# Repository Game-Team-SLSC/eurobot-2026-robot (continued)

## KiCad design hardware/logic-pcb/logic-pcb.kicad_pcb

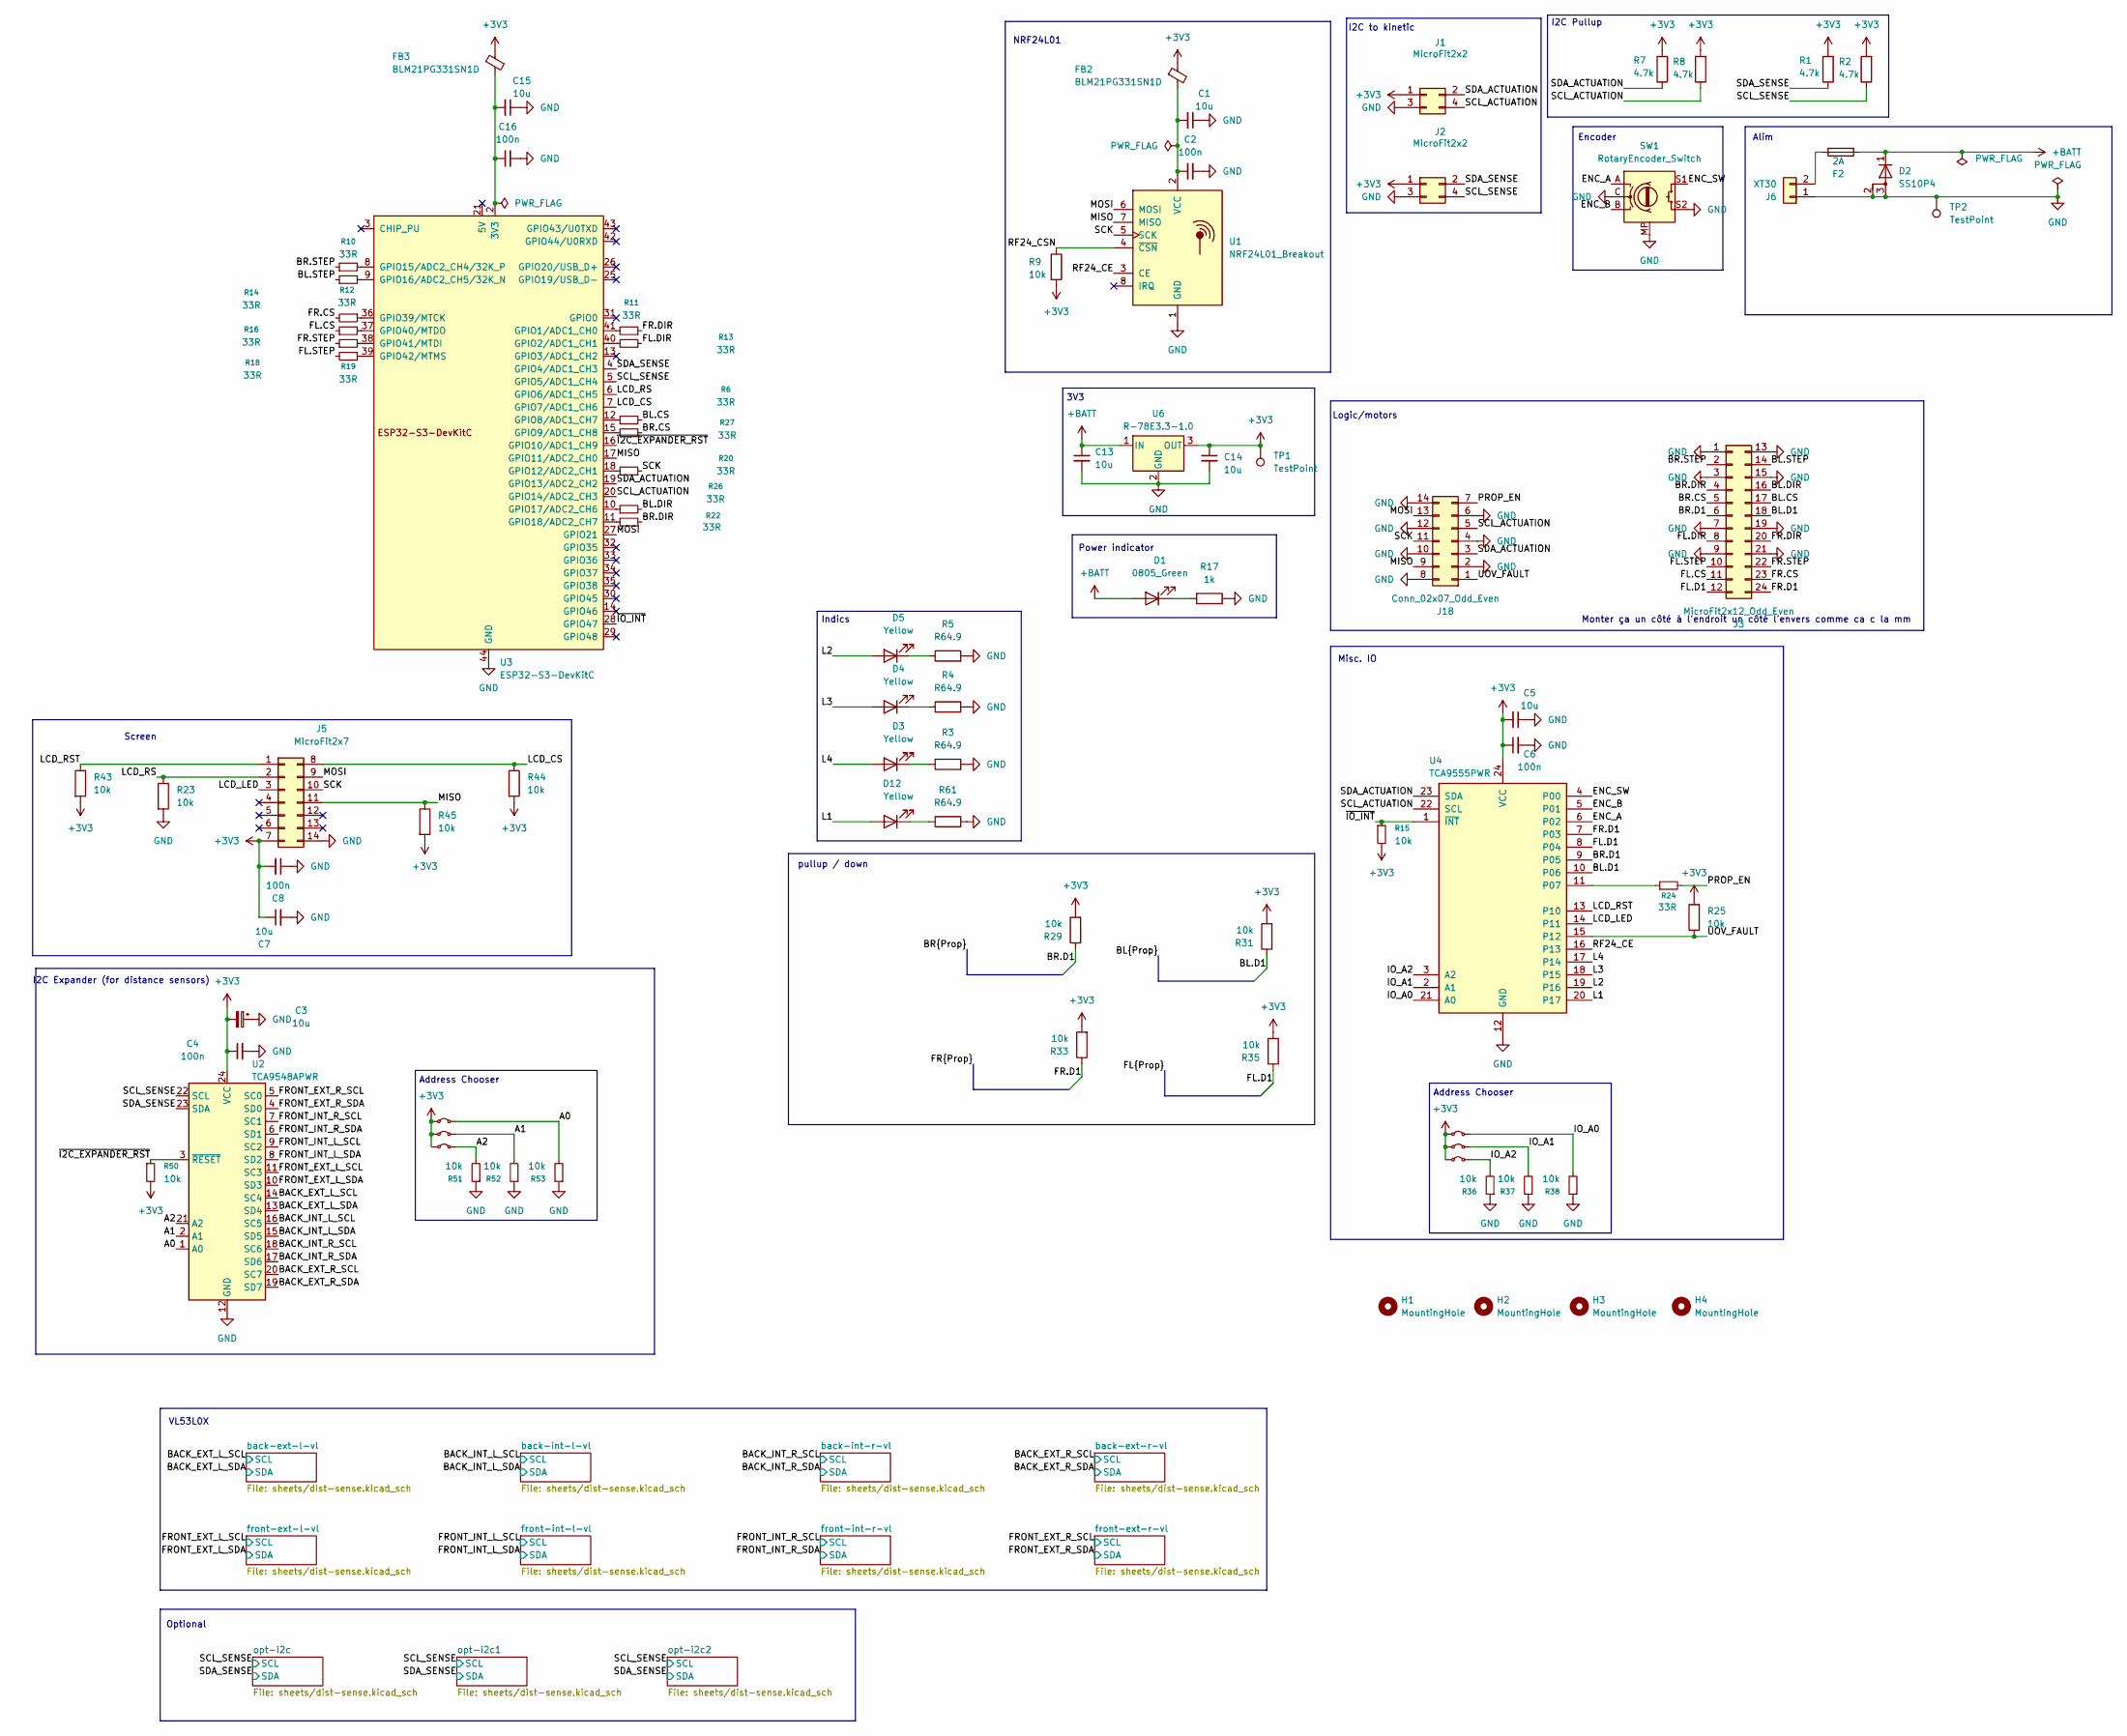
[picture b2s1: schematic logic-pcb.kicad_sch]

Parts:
C1, C3, C5, C7, C13, C14, C15: 10u; C_0805_2012Metric_Pad1.18x1.45mm_HandSolder; MPN CL21A106KBYQNNE
C2, C4, C6, C8, C16: 100n; C_0805_2012Metric_Pad1.18x1.45mm_HandSolder; MPN CL21B104KBCNNND
D1: 0805_Green; LED_0805_2012Metric_Pad1.15x1.40mm_HandSolder; MPN APA2106ZGCK
D2: SS10P4; SS10P4M387A; MPN SS10P4-M3/87A
D3, D4, D5, D12: Yellow; LED_0805_2012Metric_Pad1.15x1.40mm_HandSolder; MPN APA2106SYCK
F2: 2A; Fuseholder_Cylinder-5x20mm_Schurter_0031_8201_Horizontal_Op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
FB2, FB3: BLM21PG331SN1D; L_0805_2012Metric_Pad1.05x1.20mm_HandSolder; MPN BLM21PG331SN1D
H1, H2, H3, H4: MountingHole; MountingHole_3.2mm_M3
J1, J2: MicroFit2x2; J_Wurth_WR-MPC3_66200421122; MPN 66200421122
J3: MicroFit2x12_Odd_Even; J_Wurth_WR-MPC3_66202421122; MPN 43045-2412
J5: MicroFit2x7; J_Wurth_WR-MPC3_66201421122; MPN 43045-1412
J6: XT30; AMASS_XT30U-M_1x02_P5.0mm_Vertical
J18: Conn_02x07_Odd_Even; J_Wurth_WR-MPC3_66201421122; MPN 43045-1412
NT1, NT2, NT3, NT10, NT11, NT12: Jumper_2_Bridged; TestPoint_2Pads_Pitch2.54mm_Drill0.8mm; MPN M7582-46
R1, R2, R7, R8: 4.7k; R_0805_2012Metric_Pad1.20x1.40mm_HandSolder; MPN CRCW08054K70FKEA
R3, R4, R5, R61: R64.9; R_0805_2012Metric_Pad1.20x1.40mm_HandSolder; MPN CRCW08051K00FKEA
R6, R10, R11, R12, R13, R14, R16, R18, R19, R20, R22, R24, R26, R27: 33R; R_0805_2012Metric_Pad1.20x1.40mm_HandSolder; MPN CRCW080533R0FKEA
R9, R15, R23, R25, R29, R31, R33, R35, R36, R37, R38, R43, R44, R45, R50, R51, R52, R53: 10k; R_0805_2012Metric_Pad1.20x1.40mm_HandSolder; MPN CRCW080510K0FKEA
R17: 1k; R_0805_2012Metric_Pad1.20x1.40mm_HandSolder; MPN CRCW08051K00FKEA
SW1: RotaryEncoder_Switch; RotaryEncoder_Alps_EC11E-Switch_Vertical_H20mm; MPN EC11E15204A3
TP1, TP2: TestPoint; TestPoint_THTPad_D1.0mm_Drill0.5mm
U1: NRF24L01_Breakout; nRF24L01+_Breakout
U2: TCA9548APWR; TSSOP-24_4.4x7.8mm_P0.65mm; MPN TCA9548APWR
U3: ESP32-S3-DevKitC; MPN ESP32-S3-DevKitC-1-N8R8
U4: TCA9555PWR; TSSOP-24_4.4x7.8mm_P0.65mm; MPN TCA9555PWR
U6: R-78E3.3-1.0; Converter_DCDC_RECOM_R-78E-0.5_THT; MPN R-78E3.3-1.0

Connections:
+3V3: C3.2, C4.1, C5.2, C6.1, C7.1, C8.2, C14.1, FB2.1, FB3.1, J1.1, J2.1, J5.7, NT1.1 (A), NT2.1 (A), NT3.1 (A), NT10.1 (A), NT11.1 (A), NT12.1 (A), R1.2, R2.2, R7.2, R8.2, R9.2, R15.2, R25.2, R29.2, R31.2, R33.2, R35.2, R43.2, R44.2, R45.2, R50.2, TP1.1, U2.24 (VCC), U4.24 (VCC), U6.3 (OUT); also elsewhere on the board
+BATT: C13.1, D1.2 (A), D2.1 (K), F2.2, U6.1 (IN)
/A0: NT10.2 (B), R53.2, U2.1 (A0)
/A1: NT11.2 (B), R52.2, U2.2 (A1)
/A2: NT12.2 (B), R51.2, U2.21 (A2)
/BACK_EXT_L_SCL: U2.14 (SC4); also elsewhere on the board
/BACK_EXT_L_SDA: U2.13 (SD4); also elsewhere on the board
/BACK_EXT_R_SCL: U2.20 (SC7); also elsewhere on the board
/BACK_EXT_R_SDA: U2.19 (SD7); also elsewhere on the board
/BACK_INT_L_SCL: U2.16 (SC5); also elsewhere on the board
/BACK_INT_L_SDA: U2.15 (SD5); also elsewhere on the board
/BACK_INT_R_SCL: U2.18 (SC6); also elsewhere on the board
/BACK_INT_R_SDA: U2.17 (SD6); also elsewhere on the board
/BL.CS: J3.17, R6.2
/BL.D1: J3.18, R31.1, U4.10 (P06)
/BL.DIR: J3.16, R26.2
/BL.STEP: J3.14, R12.1
/BR.CS: J3.5, R27.2
/BR.D1: J3.6, R29.1, U4.9 (P05)
/BR.DIR: J3.4, R22.2
/BR.STEP: J3.2, R10.1
/ENC_A: SW1.A, U4.6 (P02)
/ENC_B: SW1.B, U4.5 (P01)
/ENC_SW: SW1.S1, U4.4 (P00)
/FL.CS: J3.11, R16.1
/FL.D1: J3.12, R35.1, U4.8 (P04)
/FL.DIR: J3.8, R13.1
/FL.STEP: J3.10, R19.2
/FR.CS: J3.23, R14.2
/FR.D1: J3.24, R33.1, U4.7 (P03)
/FR.DIR: J3.20, R11.1
/FR.STEP: J3.22, R18.1
/FRONT_EXT_L_SCL: U2.11 (SC3); also elsewhere on the board
/FRONT_EXT_L_SDA: U2.10 (SD3); also elsewhere on the board
/FRONT_EXT_R_SCL: U2.5 (SC0); also elsewhere on the board
/FRONT_EXT_R_SDA: U2.4 (SD0); also elsewhere on the board
/FRONT_INT_L_SCL: U2.9 (SC2); also elsewhere on the board
/FRONT_INT_L_SDA: U2.8 (SD2); also elsewhere on the board
/FRONT_INT_R_SCL: U2.7 (SC1); also elsewhere on the board
/FRONT_INT_R_SDA: U2.6 (SD1); also elsewhere on the board
/IO_A0: NT1.2 (B), R38.2, U4.21 (A0)
/IO_A1: NT2.2 (B), R37.2, U4.2 (A1)
/IO_A2: NT3.2 (B), R36.2, U4.3 (A2)
/L1: D12.2 (A), U4.20 (P17)
/L2: D5.2 (A), U4.19 (P16)
/L3: D4.2 (A), U4.18 (P15)
/L4: D3.2 (A), U4.17 (P14)
/LCD_CS: J5.8, R44.1, U3.7 (GPIO7/ADC1_CH6)
/LCD_LED: J5.3, U4.14 (P11)
/LCD_RS: J5.2, R23.1, U3.6 (GPIO6/ADC1_CH5)
/LCD_RST: J5.1, R43.1, U4.13 (P10)
/MISO: J5.11, J18.9, R45.1, U1.7 (MISO), U3.17 (GPIO11/ADC2_CH0)
/MOSI: J5.9, J18.13, U1.6 (MOSI), U3.27 (GPIO21)
/PROP_EN: J18.7, R24.2
/RF24_CE: U1.3 (CE), U4.16 (P13)
/RF24_CSN: R9.1, U1.4 (~CSN)
/SCK: J5.10, J18.11, R20.1, U1.5 (SCK)
/SCL_ACTUATION: J1.4, J18.5, R8.1, U3.20 (GPIO14/ADC2_CH3), U4.22 (SCL)
/SCL_SENSE: J2.4, R2.1, U2.22 (SCL), U3.5 (GPIO5/ADC1_CH4); also elsewhere on the board
/SDA_ACTUATION: J1.2, J18.3, R7.1, U3.19 (GPIO13/ADC2_CH2), U4.23 (SDA)
/SDA_SENSE: J2.2, R1.1, U2.23 (SDA), U3.4 (GPIO4/ADC1_CH3); also elsewhere on the board
/UOV_FAULT: J18.1, R25.1, U4.15 (P12)
/~I2C_EXPANDER_RST: R50.1, U2.3 (~RESET), U3.16 (GPIO10/ADC1_CH9)
/~IO_INT: R15.1, U3.28 (GPIO47), U4.1 (~INT)
GND: C1.1, C2.2, C3.1, C4.2, C5.1, C6.2, C7.2, C8.1, C13.2, C14.2, C15.1, C16.2, D2.2 (A), D2.3 (A), J1.3, J2.3, J3.1, J3.3, J3.7, J3.9, J3.13, J3.15, J3.19, J3.21, J5.14, J6.1, J18.2, J18.4, J18.6, J18.8, J18.10, J18.12, J18.14, R3.2, R4.2, R5.2, R17.2, R23.2, R36.1, R37.1, R38.1, R51.1, R52.1, R53.1, R61.2, SW1.C, SW1.MP, SW1.S2, TP2.1, U1.1 (GND), U2.12 (GND), U3.22 (GND), U3.23 (GND), U3.24 (GND), U3.44 (GND), U4.12 (GND), U6.2 (GND); also elsewhere on the board
unnamed: C15.2, C16.1, FB3.2, U3.1 (3V3), U3.2 (3V3)
unnamed: D1.1 (K), R17.1
unnamed: D3.1 (K), R3.1
unnamed: D4.1 (K), R4.1
unnamed: D5.1 (K), R5.1
unnamed: D12.1 (K), R61.1
unnamed: F2.1, J6.2
unnamed: C1.2, C2.1, FB2.2, U1.2 (VCC)
unnamed: R11.2, U3.41 (GPIO1/ADC1_CH0)
unnamed: R13.2, U3.40 (GPIO2/ADC1_CH1)
unnamed: R6.1, U3.12 (GPIO8/ADC1_CH7)
unnamed: R27.1, U3.15 (GPIO9/ADC1_CH8)
unnamed: R20.2, U3.18 (GPIO12/ADC2_CH1)
unnamed: R10.2, U3.8 (GPIO15/ADC2_CH4/32K_P)
unnamed: R12.2, U3.9 (GPIO16/ADC2_CH5/32K_N)
unnamed: R26.1, U3.10 (GPIO17/ADC2_CH6)
unnamed: R22.1, U3.11 (GPIO18/ADC2_CH7)
unnamed: R14.1, U3.36 (GPIO39/MTCK)
unnamed: R16.2, U3.37 (GPIO40/MTDO)
unnamed: R18.2, U3.38 (GPIO41/MTDI)
unnamed: R19.1, U3.39 (GPIO42/MTMS)
unnamed: R24.1, U4.11 (P07)

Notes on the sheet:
Address Chooser
VL53L0X
I2C Expander (for distance sensors)
Monter ça un côté à l'endroit un côté l'envers comme ca c la mm
Logic/motors
Indics
Alim
3V3
I2C Pullup
Misc. IO
pullup / down
Optional
Screen
NRF24L01
Encoder
Power indicator
I2C to kinetic

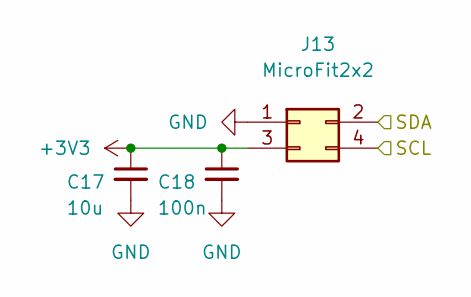
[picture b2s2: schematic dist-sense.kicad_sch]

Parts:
C17: 10u; C_0805_2012Metric_Pad1.18x1.45mm_HandSolder; MPN CL21A106KBYQNNE
C18: 100n; C_0805_2012Metric_Pad1.18x1.45mm_HandSolder; MPN CL21B104KBCNNND
J13: MicroFit2x2; J_Wurth_WR-MPC3_66200421122; MPN 66200421122

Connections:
+3V3: C17.1, C18.1, J13.3; also elsewhere on the board
/BACK_EXT_L_SCL: J13.4; also elsewhere on the board
/BACK_EXT_L_SDA: J13.2; also elsewhere on the board
GND: C17.2, C18.2, J13.1; also elsewhere on the board

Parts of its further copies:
C19, C21, C23, C25, C27, C29, C31, C33, C35, C37: 10u; C_0805_2012Metric_Pad1.18x1.45mm_HandSolder; MPN CL21A106KBYQNNE
C20, C22, C24, C26, C28, C30, C32, C34, C36, C38: 100n; C_0805_2012Metric_Pad1.18x1.45mm_HandSolder; MPN CL21B104KBCNNND
J7, J8, J9, J10, J11, J12, J14, J15, J16, J17: MicroFit2x2; J_Wurth_WR-MPC3_66200421122; MPN 66200421122

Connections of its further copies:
+3V3: C19.1, C20.1, C21.1, C22.1, C23.1, C24.1, C25.1, C26.1, C27.1, C28.1, C29.1, C30.1, C31.1, C32.1, C33.1, C34.1, C35.1, C36.1, C37.1, C38.1, J7.3, J8.3, J9.3, J10.3, J11.3, J12.3, J14.3, J15.3, J16.3, J17.3; also elsewhere on the board
/BACK_EXT_R_SCL: J12.4; also elsewhere on the board
/BACK_EXT_R_SDA: J12.2; also elsewhere on the board
/BACK_INT_L_SCL: J8.4; also elsewhere on the board
/BACK_INT_L_SDA: J8.2; also elsewhere on the board
/BACK_INT_R_SCL: J10.4; also elsewhere on the board
/BACK_INT_R_SDA: J10.2; also elsewhere on the board
/FRONT_EXT_L_SCL: J7.4; also elsewhere on the board
/FRONT_EXT_L_SDA: J7.2; also elsewhere on the board
/FRONT_EXT_R_SCL: J14.4; also elsewhere on the board
/FRONT_EXT_R_SDA: J14.2; also elsewhere on the board
/FRONT_INT_L_SCL: J9.4; also elsewhere on the board
/FRONT_INT_L_SDA: J9.2; also elsewhere on the board
/FRONT_INT_R_SCL: J11.4; also elsewhere on the board
/FRONT_INT_R_SDA: J11.2; also elsewhere on the board
/SCL_SENSE: J15.4, J16.4, J17.4; also elsewhere on the board
/SDA_SENSE: J15.2, J16.2, J17.2; also elsewhere on the board
GND: C19.2, C20.2, C21.2, C22.2, C23.2, C24.2, C25.2, C26.2, C27.2, C28.2, C29.2, C30.2, C31.2, C32.2, C33.2, C34.2, C35.2, C36.2, C37.2, C38.2, J7.1, J8.1, J9.1, J10.1, J11.1, J12.1, J14.1, J15.1, J16.1, J17.1; also elsewhere on the board

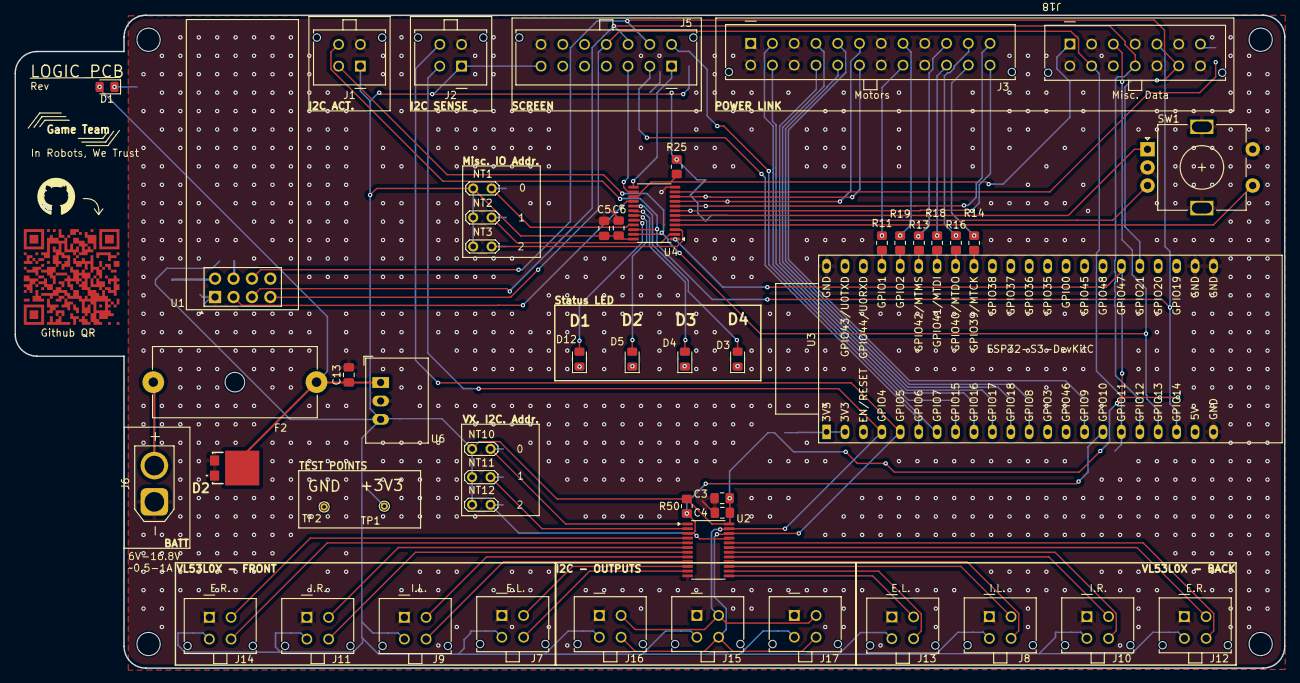
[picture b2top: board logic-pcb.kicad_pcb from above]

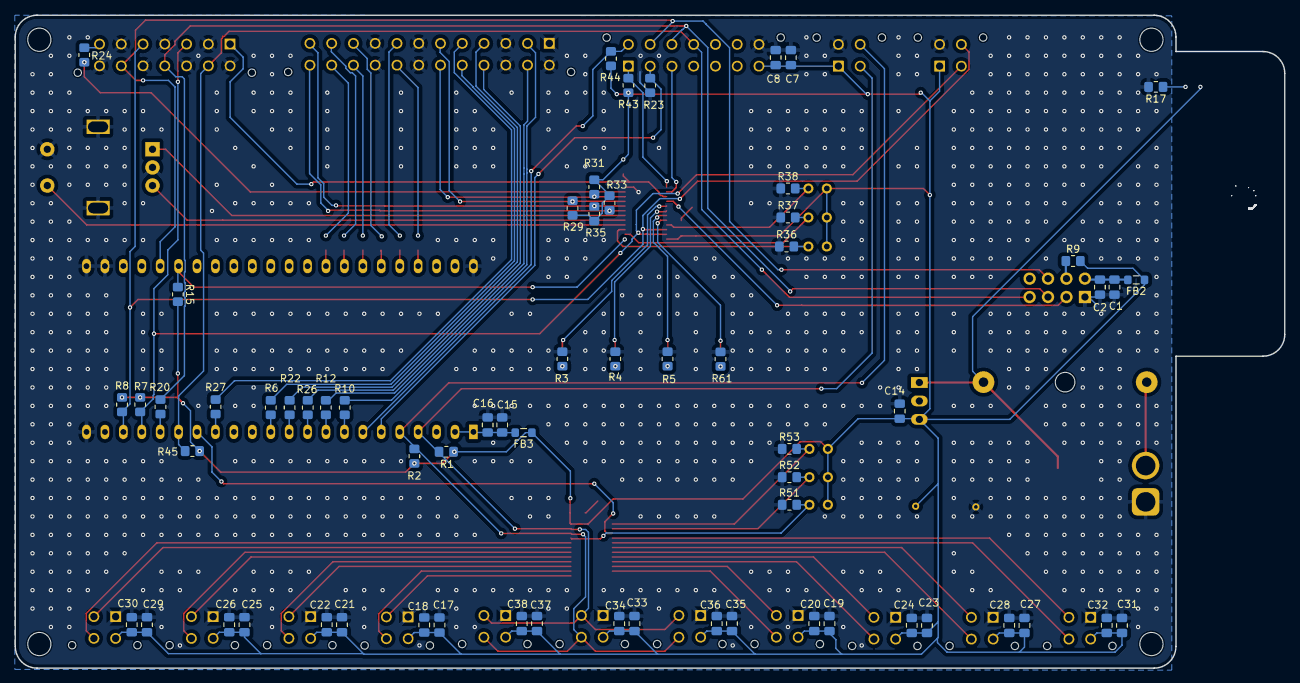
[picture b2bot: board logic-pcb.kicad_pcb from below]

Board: 2 copper layers, 175.0 x 90.0 mm, 120 parts (64 on the bottom side), 87 nets.

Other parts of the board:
QR*****: Github QR

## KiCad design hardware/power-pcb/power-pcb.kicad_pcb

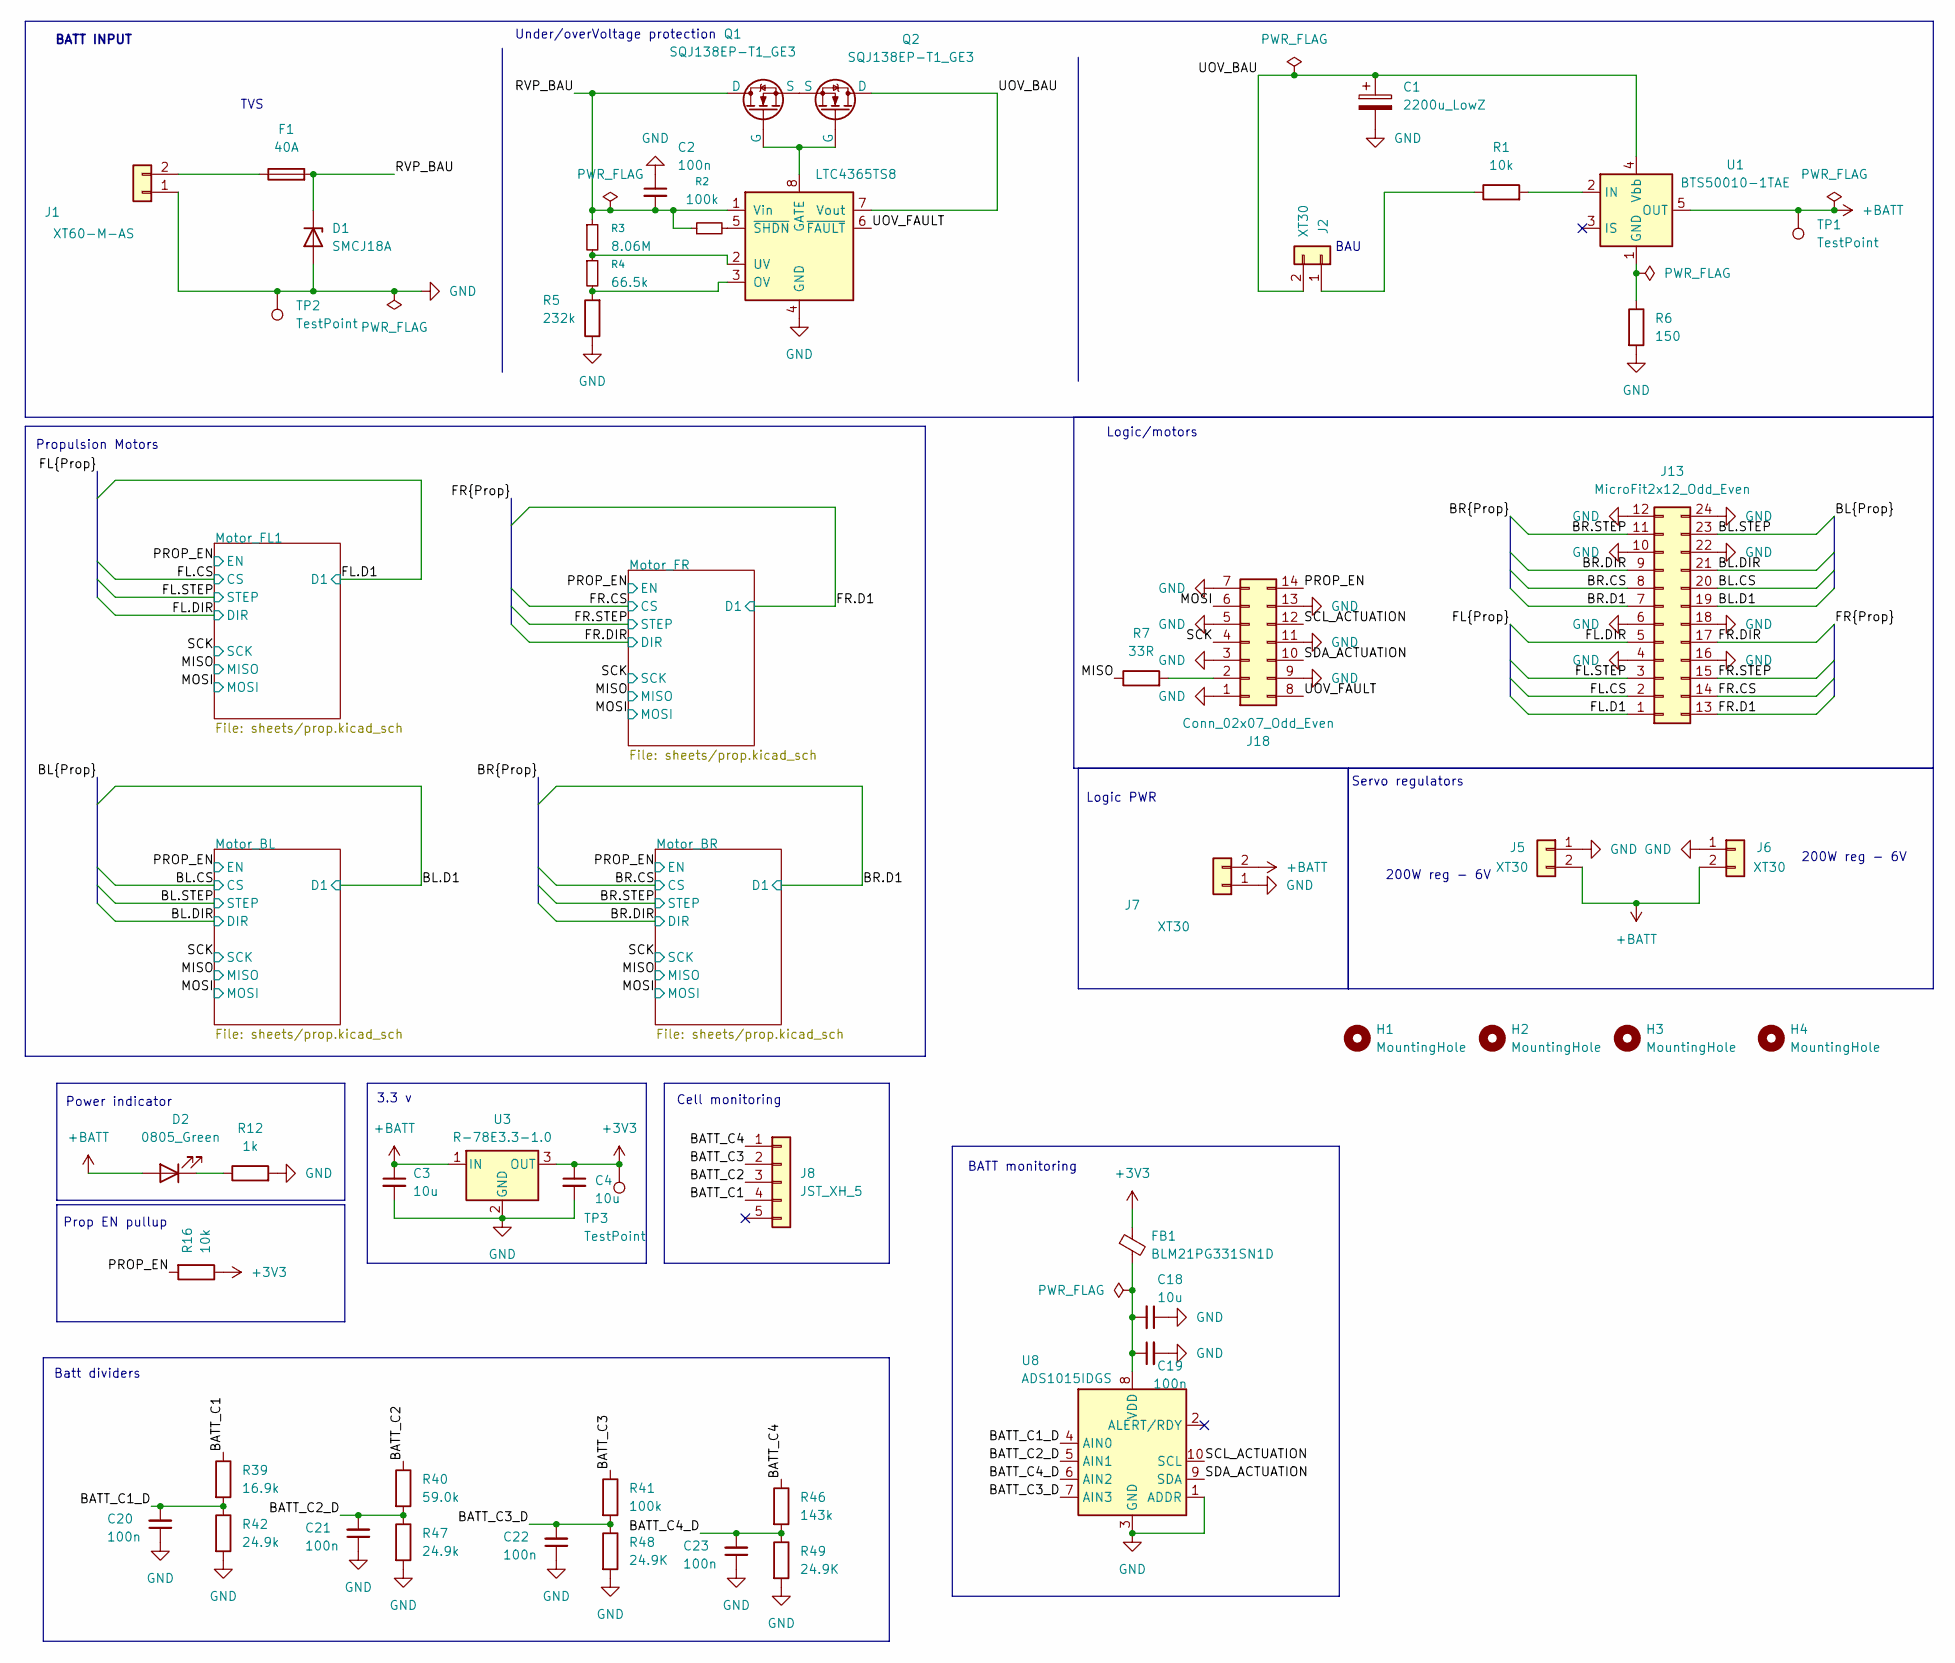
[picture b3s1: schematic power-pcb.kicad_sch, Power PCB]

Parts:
C1: 2200u_LowZ; CP_Radial_D16.0mm_P7.50mm; MPN EEUFR1V222
C2, C19, C20, C21, C22, C23: 100n; C_0805_2012Metric_Pad1.18x1.45mm_HandSolder; MPN CL21B104KBCNNND
C3, C4, C18: 10u; C_0805_2012Metric_Pad1.18x1.45mm_HandSolder; MPN CL21A106KBYQNNE
D1: SMCJ18A; D_SMB-SMC_Universal_Handsoldering; MPN SMCJ18A-E3/9AT
D2: 0805_Green; LED_0805_2012Metric_Pad1.15x1.40mm_HandSolder; MPN APA2106ZGCK
F1: 40A; Fuseholder_Cylinder-5x20mm_Schurter_0031_8201_Horizontal_Op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
FB1: BLM21PG331SN1D; L_0805_2012Metric_Pad1.05x1.20mm_HandSolder; MPN BLM21PG331SN1D
H1, H2, H3, H4: MountingHole; MountingHole_3.2mm_M3
J1: XT60-M-AS; AMASS_XT60-M_1x02_P7.20mm_Vertical
J2, J5, J6, J7: XT30; AMASS_XT30U-M_1x02_P5.0mm_Vertical
J8: JST_XH_5; JST_XH_B5B-XH-AM_1x05_P2.50mm_Vertical; MPN B5B-XH-A-G
J13: MicroFit2x12_Odd_Even; J_Wurth_WR-MPC3_66202421122; MPN 43045-2412
J18: Conn_02x07_Odd_Even; J_Wurth_WR-MPC3_66201421122; MPN 43045-1412
Q1, Q2: SQJ138EP-T1_GE3; PowerPAK_SO-8L_Single_MOS; MPN SQJ138EP-T1_GE3
R1, R16: 10k; R_0805_2012Metric_Pad1.20x1.40mm_HandSolder; MPN CRCW080510K0FKEA
R2, R41: 100k; R_0805_2012Metric_Pad1.20x1.40mm_HandSolder; MPN CRCW0805100KFKEA
R3: 8.06M; R_0805_2012Metric_Pad1.20x1.40mm_HandSolder; MPN RC0805FR-078M06L
R4: 66.5k; R_0805_2012Metric_Pad1.20x1.40mm_HandSolder; MPN CRCW080566K5FKEA
R5: 232k; R_0805_2012Metric_Pad1.20x1.40mm_HandSolder; MPN CRCW0805232KFKEA
R6: 150; R_0805_2012Metric_Pad1.20x1.40mm_HandSolder; MPN CRCW0805150RFKEA
R7: 33R; R_0805_2012Metric_Pad1.20x1.40mm_HandSolder; MPN CRCW080533R0FKEA
R12: 1k; R_0805_2012Metric_Pad1.20x1.40mm_HandSolder; MPN CRCW08051K00FKEA
R39: 16.9k; R_0805_2012Metric_Pad1.20x1.40mm_HandSolder; MPN CRCW080516K9FKEA
R40: 59.0k; R_0805_2012Metric_Pad1.20x1.40mm_HandSolder; MPN CRCW080559K0FKEA
R42, R47: 24.9k; R_0805_2012Metric_Pad1.20x1.40mm_HandSolder; MPN CRCW080524K9FKEA
R46: 143k; R_0805_2012Metric_Pad1.20x1.40mm_HandSolder; MPN CRCW0805143KFKEA
R48, R49: 24.9K; R_0805_2012Metric_Pad1.20x1.40mm_HandSolder; MPN CRCW080524K9FKEA
TP1, TP2, TP3: TestPoint; TestPoint_THTPad_D1.0mm_Drill0.5mm
U1: BTS50010-1TAE; TO-263-7_TabPin4; MPN BTS500101TAEATMA1
U2: LTC4365TS8; TSOT-23-8_HandSoldering; MPN LTC4365ITS8-1#TRMPBF
U3: R-78E3.3-1.0; Converter_DCDC_RECOM_R-78E-0.5_THT; MPN R-78E3.3-1.0
U8: ADS1015IDGS; TSSOP-10_3x3mm_P0.5mm; MPN ADS1015IDGS

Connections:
+3V3: C4.1, FB1.1, R16.1, TP3.1, U3.3 (OUT); also elsewhere on the board
+BATT: C3.1, D2.2 (A), J5.2, J6.2, J7.2, TP1.1, U1.5 (OUT), U1.6 (OUT), U1.7 (OUT), U3.1 (IN); also elsewhere on the board
/BATT_C1: J8.4, R39.1
/BATT_C1_D: C20.2, R39.2, R42.1, U8.4 (AIN0)
/BATT_C2: J8.3, R40.1
/BATT_C2_D: C21.2, R40.2, R47.1, U8.5 (AIN1)
/BATT_C3: J8.2, R41.1
/BATT_C3_D: C22.2, R41.2, R48.1, U8.7 (AIN3)
/BATT_C4: J8.1, R46.1
/BATT_C4_D: C23.2, R46.2, R49.1, U8.6 (AIN2)
/BL.CS: J13.20; also elsewhere on the board
/BL.D1: J13.19; also elsewhere on the board
/BL.DIR: J13.21; also elsewhere on the board
/BL.STEP: J13.23; also elsewhere on the board
/BR.CS: J13.8; also elsewhere on the board
/BR.D1: J13.7; also elsewhere on the board
/BR.DIR: J13.9; also elsewhere on the board
/BR.STEP: J13.11; also elsewhere on the board
/FL.CS: J13.2; also elsewhere on the board
/FL.D1: J13.1; also elsewhere on the board
/FL.DIR: J13.5; also elsewhere on the board
/FL.STEP: J13.3; also elsewhere on the board
/FR.CS: J13.14; also elsewhere on the board
/FR.D1: J13.13; also elsewhere on the board
/FR.DIR: J13.17; also elsewhere on the board
/FR.STEP: J13.15; also elsewhere on the board
/MISO: R7.1; also elsewhere on the board
/MOSI: J18.6; also elsewhere on the board
/PROP_EN: J18.14, R16.2; also elsewhere on the board
/RVP_BAU: C2.2, D1.1 (K), F1.2, Q1.1 (D), R2.1, R3.1, U2.1 (Vin)
/SCK: J18.4; also elsewhere on the board
/SCL_ACTUATION: J18.12, U8.10 (SCL)
/SDA_ACTUATION: J18.10, U8.9 (SDA)
/UOV_BAU: C1.1, J2.2, Q2.1 (D), U1.4 (Vbb), U2.7 (Vout)
/UOV_FAULT: J18.8, U2.6 (~FAULT)
GND: C1.2, C2.1, C3.2, C4.2, C18.1, C19.2, C20.1, C21.1, C22.1, C23.1, D1.2 (A), J1.1, J5.1, J6.1, J7.1, J13.4, J13.6, J13.10, J13.12, J13.16, J13.18, J13.22, J13.24, J18.1, J18.3, J18.5, J18.7, J18.9, J18.11, J18.13, R5.1, R6.2, R12.2, R42.2, R47.2, R48.2, R49.2, TP2.1, U2.4 (GND), U3.2 (GND), U8.1 (ADDR), U8.3 (GND); also elsewhere on the board
unnamed: D2.1 (K), R12.1
unnamed: F1.1, J1.2
unnamed: J2.1, R1.1
unnamed: J18.2, R7.2
unnamed: Q1.2 (G), Q2.2 (G), U2.8 (GATE)
unnamed: Q1.3 (S), Q2.3 (S)
unnamed: R6.1, U1.1 (GND)
unnamed: R1.2, U1.2 (IN)
unnamed: R4.2, R5.2, U2.3 (OV)
unnamed: R3.2, R4.1, U2.2 (UV)
unnamed: R2.2, U2.5 (~SHDN)
unnamed: C18.2, C19.1, FB1.2, U8.8 (VDD)

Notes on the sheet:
200W reg - 6V
Power indicator
Prop EN pullup
BAU
Logic PWR
Batt dividers
Cell monitoring
BATT INPUT
Logic/motors
Under/overVoltage protection
200W reg - 6V
TVS
Propulsion Motors
3.3 v
BATT monitoring
Servo regulators

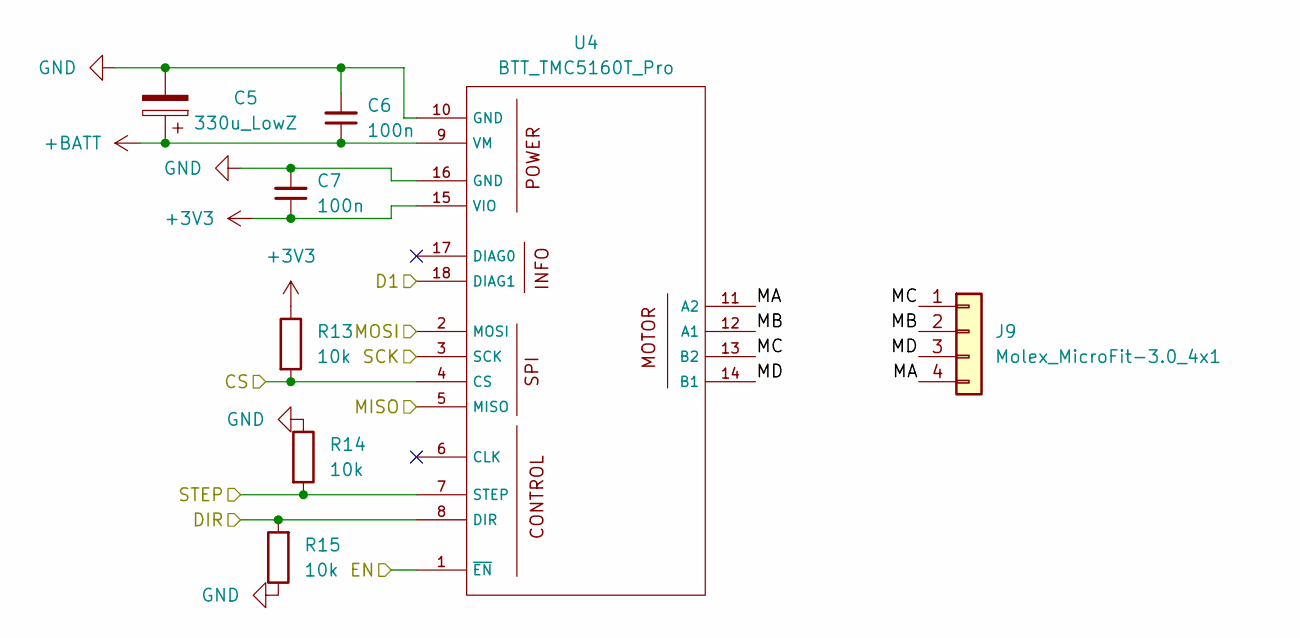
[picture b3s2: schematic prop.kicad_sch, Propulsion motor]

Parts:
C5: 330u_LowZ; CP_Radial_D10.0mm_P5.00mm; MPN EEUFR1V331U
C6, C7: 100n; C_0805_2012Metric_Pad1.18x1.45mm_HandSolder; MPN CL21B104KBCNNND
J9: Molex_MicroFit-3.0_4x1; J_Wurth_WR-MPC3_66200421122; MPN 66200421122
R13, R14, R15: 10k; R_0805_2012Metric_Pad1.20x1.40mm_HandSolder; MPN CRCW080510K0FKEA
U4: BTT_TMC5160T_Pro

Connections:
+3V3: C7.1, R13.1, U4.15 (VIO); also elsewhere on the board
+BATT: C5.1, C6.1, U4.9 (VM); also elsewhere on the board
/BL.CS: R13.2, U4.4 (CS); also elsewhere on the board
/BL.D1: U4.18 (DIAG1); also elsewhere on the board
/BL.DIR: R15.2, U4.8 (DIR); also elsewhere on the board
/BL.STEP: R14.2, U4.7 (STEP); also elsewhere on the board
/MISO: U4.5 (MISO); also elsewhere on the board
/MOSI: U4.2 (MOSI); also elsewhere on the board
/Motor_BL/MA: J9.4, U4.11 (A2)
/Motor_BL/MB: J9.2, U4.12 (A1)
/Motor_BL/MC: J9.1, U4.13 (B2)
/Motor_BL/MD: J9.3, U4.14 (B1)
/PROP_EN: U4.1 (~EN); also elsewhere on the board
/SCK: U4.3 (SCK); also elsewhere on the board
GND: C5.2, C6.2, C7.2, R14.1, R15.1, U4.10 (GND), U4.16 (GND); also elsewhere on the board

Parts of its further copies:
C8, C11, C14: 330u_LowZ; CP_Radial_D10.0mm_P5.00mm; MPN EEUFR1V331U
C9, C10, C12, C13, C15, C16: 100n; C_0805_2012Metric_Pad1.18x1.45mm_HandSolder; MPN CL21B104KBCNNND
J10, J11, J12: Molex_MicroFit-3.0_4x1; J_Wurth_WR-MPC3_66200421122; MPN 66200421122
R17, R18, R19, R21, R22, R23, R25, R26, R27: 10k; R_0805_2012Metric_Pad1.20x1.40mm_HandSolder; MPN CRCW080510K0FKEA
U5, U6, U7: BTT_TMC5160T_Pro

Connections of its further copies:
+3V3: C10.1, C13.1, C16.1, R17.1, R21.1, R25.1, U5.15 (VIO), U6.15 (VIO), U7.15 (VIO); also elsewhere on the board
+BATT: C8.1, C9.1, C11.1, C12.1, C14.1, C15.1, U5.9 (VM), U6.9 (VM), U7.9 (VM); also elsewhere on the board
/BR.CS: R17.2, U5.4 (CS); also elsewhere on the board
/BR.D1: U5.18 (DIAG1); also elsewhere on the board
/BR.DIR: R19.2, U5.8 (DIR); also elsewhere on the board
/BR.STEP: R18.2, U5.7 (STEP); also elsewhere on the board
/FL.CS: R21.2, U6.4 (CS); also elsewhere on the board
/FL.D1: U6.18 (DIAG1); also elsewhere on the board
/FL.DIR: R23.2, U6.8 (DIR); also elsewhere on the board
/FL.STEP: R22.2, U6.7 (STEP); also elsewhere on the board
/FR.CS: R25.2, U7.4 (CS); also elsewhere on the board
/FR.D1: U7.18 (DIAG1); also elsewhere on the board
/FR.DIR: R27.2, U7.8 (DIR); also elsewhere on the board
/FR.STEP: R26.2, U7.7 (STEP); also elsewhere on the board
/MISO: U5.5 (MISO), U6.5 (MISO), U7.5 (MISO); also elsewhere on the board
/MOSI: U5.2 (MOSI), U6.2 (MOSI), U7.2 (MOSI); also elsewhere on the board
/Motor_BR/MA: J10.4, U5.11 (A2)
/Motor_BR/MB: J10.2, U5.12 (A1)
/Motor_BR/MC: J10.1, U5.13 (B2)
/Motor_BR/MD: J10.3, U5.14 (B1)
/Motor_FL1/MA: J11.4, U6.11 (A2)
/Motor_FL1/MB: J11.2, U6.12 (A1)
/Motor_FL1/MC: J11.1, U6.13 (B2)
/Motor_FL1/MD: J11.3, U6.14 (B1)
/Motor_FR/MA: J12.4, U7.11 (A2)
/Motor_FR/MB: J12.2, U7.12 (A1)
/Motor_FR/MC: J12.1, U7.13 (B2)
/Motor_FR/MD: J12.3, U7.14 (B1)
/PROP_EN: U5.1 (~EN), U6.1 (~EN), U7.1 (~EN); also elsewhere on the board
/SCK: U5.3 (SCK), U6.3 (SCK), U7.3 (SCK); also elsewhere on the board
GND: C8.2, C9.2, C10.2, C11.2, C12.2, C13.2, C14.2, C15.2, C16.2, R18.1, R19.1, R22.1, R23.1, R26.1, R27.1, U5.10 (GND), U5.16 (GND), U6.10 (GND), U6.16 (GND), U7.10 (GND), U7.16 (GND); also elsewhere on the board

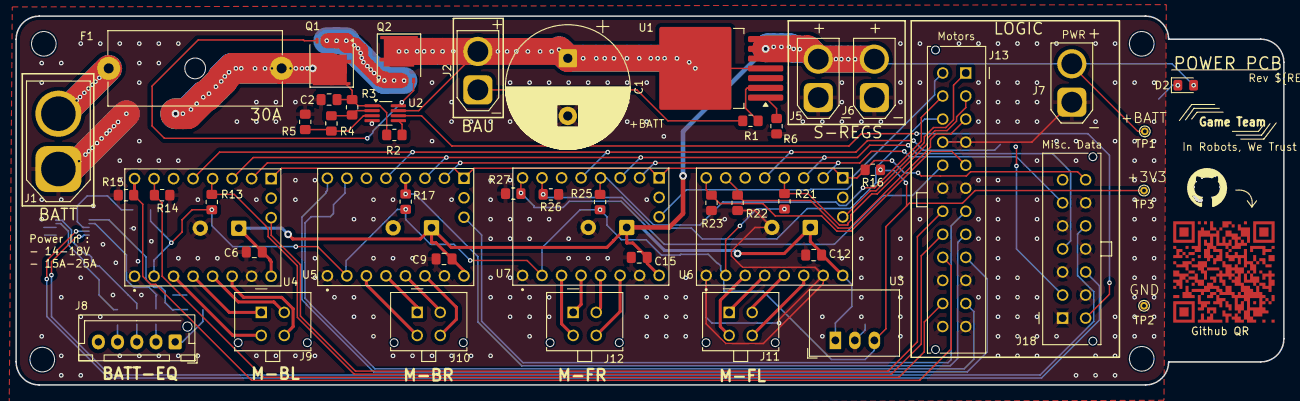
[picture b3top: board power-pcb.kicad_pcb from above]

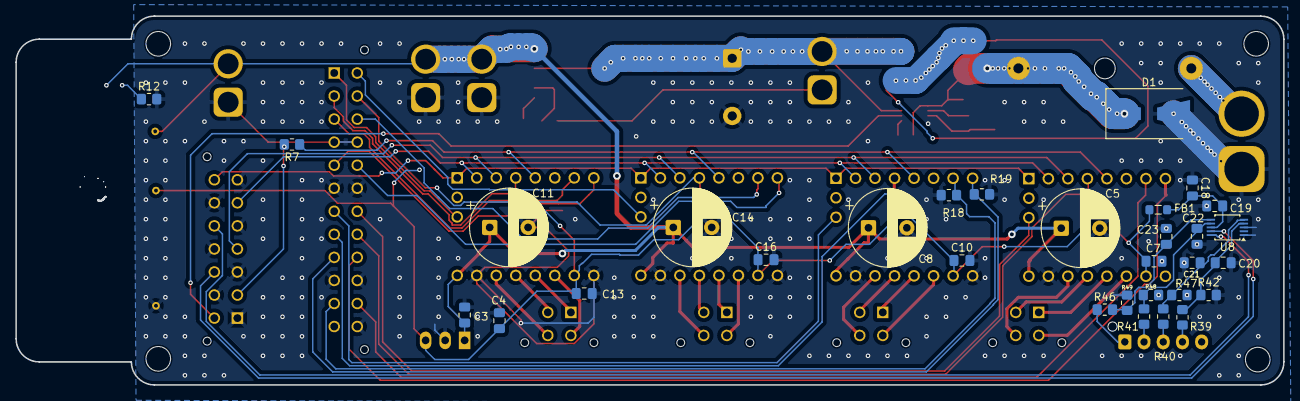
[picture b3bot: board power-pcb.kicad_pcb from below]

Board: 2 copper layers, 165.0 x 48.0 mm, 85 parts (31 on the bottom side), 64 nets.

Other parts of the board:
QR*****: Github QR
